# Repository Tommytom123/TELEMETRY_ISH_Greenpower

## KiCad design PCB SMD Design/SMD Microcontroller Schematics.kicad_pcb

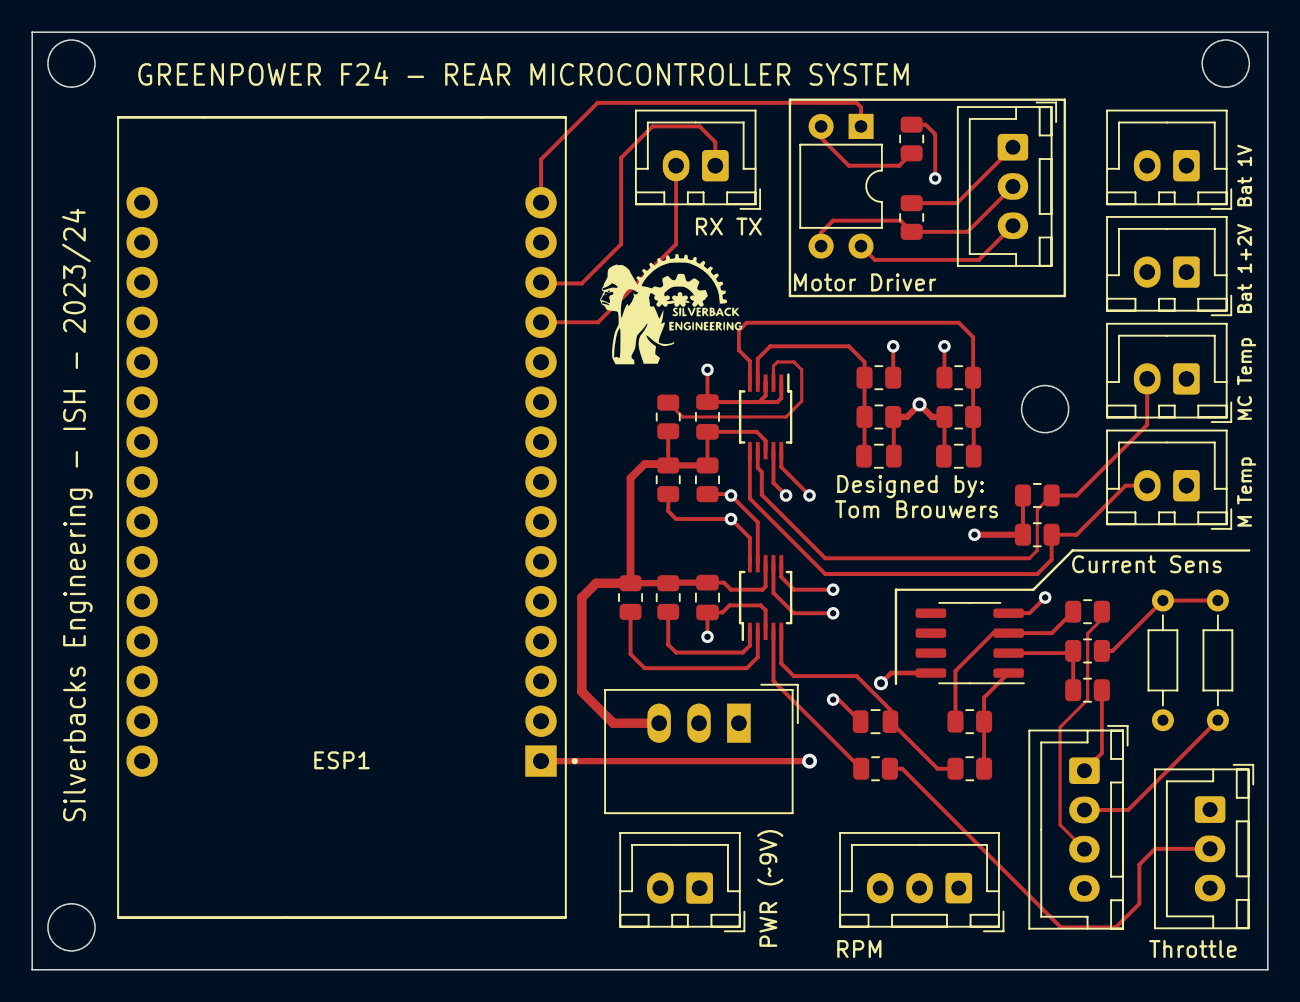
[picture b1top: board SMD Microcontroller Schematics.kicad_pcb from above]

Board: 4 copper layers, 78.7 x 59.7 mm, 42 parts (0 on the bottom side), 32 nets.

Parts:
C1, C2: C; C_0805_2012Metric
C3: 1u; C_0805_2012Metric
C4, C5: 100nF; C_0805_2012Metric
ESP1: ESP32-DEVKIT-V1; MODULE_ESP32_DEVKIT_V1
J1: Power (9v); JST_XH_B2B-XH-A_1x02_P2.50mm_Vertical
J2: Data (RX TX); JST_XH_B2B-XH-A_1x02_P2.50mm_Vertical
J3: RPM Sensor; JST_XH_B3B-XH-A_1x03_P2.50mm_Vertical
J4: Bat 1V; JST_XH_B2B-XH-A_1x02_P2.50mm_Vertical
J5: Bat 1+2 V; JST_XH_B2B-XH-A_1x02_P2.50mm_Vertical
J6: Motor Temp; JST_XH_B2B-XH-A_1x02_P2.50mm_Vertical
J7: Motor Controller Temp; JST_XH_B2B-XH-A_1x02_P2.50mm_Vertical
J8: Current Sensor; JST_XH_B4B-XH-A_1x04_P2.50mm_Vertical
J9: Motor Controller; JST_XH_B3B-XH-A_1x03_P2.50mm_Vertical
J10: Throttle HallEffect; JST_XH_B3B-XH-A_1x03_P2.50mm_Vertical
R1, R2, R3, R4, R5, R6: R; R_0805_2012Metric
R7, R8: 4.7k; R_0805_2012Metric
R9, R10, R15, R16, R17, R18, R19: 10k; R_0805_2012Metric
R11: 47k; R_0805_2012Metric
R12, R14: 1k; R_0805_2012Metric
R13: 220; R_0805_2012Metric
R20, R21: ?; R_Axial_DIN0204_L3.6mm_D1.6mm_P7.62mm_Horizontal
U1: TSR_1-2450; Converter_DCDC_TRACO_TSR-1_THT
U2: MCP6002DRG; SOIC-8_3.9x4.9mm_P1.27mm
U3: PC817; DIP-4_W7.62mm
U4, U5: ADS1115IDGS; TSSOP-10_3x3mm_P0.5mm

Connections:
3.3V: ESP1.1 (3V3), J3.3, R5.1, R6.1
5V: C4.1, C5.1, J8.4, J10.3, R15.1, R16.1, R17.1, R18.1, R19.1, U1.3 (Vout), U2.8 (V+), U4.8 (VDD), U5.8 (VDD)
9V: ESP1.30 (VIN), J1.2, U1.1 (Vin)
/Data: J9.2, R12.1, U3.3
/Motor5V: J9.3, U3.4
/MotorGND: J9.1, R12.2
Current: C3.1, R11.1, U5.5 (AIN1)
GND: C1.2, C2.2, C3.2, C4.2, C5.2, ESP1.2 (GND), ESP1.29 (GND), J1.1, J3.1, J4.1, J5.1, J6.1, J7.1, J8.1, J10.1, R2.2, R4.2, R9.2, R13.1, R21.1, U1.2 (GND), U2.4 (V-), U4.1 (ADDR), U4.3 (GND), U5.3 (GND)
GP19: ESP1.10 (D19), J3.2
GPIO 27 - PWM: ESP1.15 (D23), U3.1
Motor Controller Temp: J7.2, R6.2, U4.7 (AIN3)
Motor Temp: J6.2, R5.2, U4.6 (AIN2)
unnamed: ESP1.12 (RX0), J2.2
unnamed: ESP1.13 (TX0), J2.1
unnamed: J4.2, R1.1
unnamed: J5.2, R3.1
unnamed: J8.2, R20.1
unnamed: J8.3, R7.2
unnamed: J10.2, R14.1
unnamed: R10.1, R11.2, U2.1
unnamed: R13.2, U3.2
unnamed: R8.2, R20.2, R21.2
unnamed: R7.1, R10.2, U2.3 (+)
unnamed: R8.1, R9.1, U2.2 (-)
unnamed: R16.2, U4.2 (ALERT/RDY)
unnamed: R17.2, U5.1 (ADDR)
unnamed: R14.2, U5.4 (AIN0)
unnamed: R15.2, U5.2 (ALERT/RDY)
Reduced Bat1V: C1.1, R1.2, R2.1, U4.4 (AIN0)
Reduced TotalV: C2.1, R3.2, R4.1, U4.5 (AIN1)
SCL: ESP1.14 (D22), R18.2, U4.10 (SCL), U5.10 (SCL)
SDA: ESP1.11 (D21), R19.2, U4.9 (SDA), U5.9 (SDA)

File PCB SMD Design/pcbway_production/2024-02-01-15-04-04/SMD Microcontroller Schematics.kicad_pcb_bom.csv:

designator,quantity,value,pack,mpn,mount_type
"C1, C2",2,C,C_0805_2012Metric,,smt
C3,1,1u,C_0805_2012Metric,,smt
"C4, C5",2,100nF,C_0805_2012Metric,,smt
ESP1,1,ESP32-DEVKIT-V1,MODULE_ESP32_DEVKIT_V1,,tht
J1,1,Power (9v),JST_XH_B2B-XH-A_1x02_P2.50mm_Vertical,,tht
J10,1,Throttle HallEffect,JST_XH_B3B-XH-A_1x03_P2.50mm_Vertical,,tht
J2,1,Data (RX TX),JST_XH_B2B-XH-A_1x02_P2.50mm_Vertical,,tht
J3,1,RPM Sensor,JST_XH_B3B-XH-A_1x03_P2.50mm_Vertical,,tht
J4,1,Bat 1V,JST_XH_B2B-XH-A_1x02_P2.50mm_Vertical,,tht
J5,1,Bat 1+2 V,JST_XH_B2B-XH-A_1x02_P2.50mm_Vertical,,tht
J6,1,Motor Temp,JST_XH_B2B-XH-A_1x02_P2.50mm_Vertical,,tht
J7,1,Motor Controller Temp,JST_XH_B2B-XH-A_1x02_P2.50mm_Vertical,,tht
J8,1,Current Sensor,JST_XH_B4B-XH-A_1x04_P2.50mm_Vertical,,tht
J9,1,Motor Controller,JST_XH_B3B-XH-A_1x03_P2.50mm_Vertical,,tht
"R1, R2, R3, R4, R5, R6",6,R,R_0805_2012Metric,,smt
"R10, R15, R16, R17, R18, R19, R9",7,10k,R_0805_2012Metric,,smt
R11,1,47k,R_0805_2012Metric,,smt
"R12, R14",2,1k,R_0805_2012Metric,,smt
R13,1,220,R_0805_2012Metric,,smt
"R20, R21",2,?,R_Axial_DIN0204_L3.6mm_D1.6mm_P7.62mm_Horizontal,,tht
"R7, R8",2,4.7k,R_0805_2012Metric,,smt
U1,1,TSR_1-2450,Converter_DCDC_TRACO_TSR-1_THT,,tht
U2,1,MCP6002-xP,SOIC-8_3.9x4.9mm_P1.27mm,,smt
U3,1,PC817,DIP-4_W7.62mm,,tht
"U4, U5",2,ADS1115IDGS,TSSOP-10_3x3mm_P0.5mm,,smt

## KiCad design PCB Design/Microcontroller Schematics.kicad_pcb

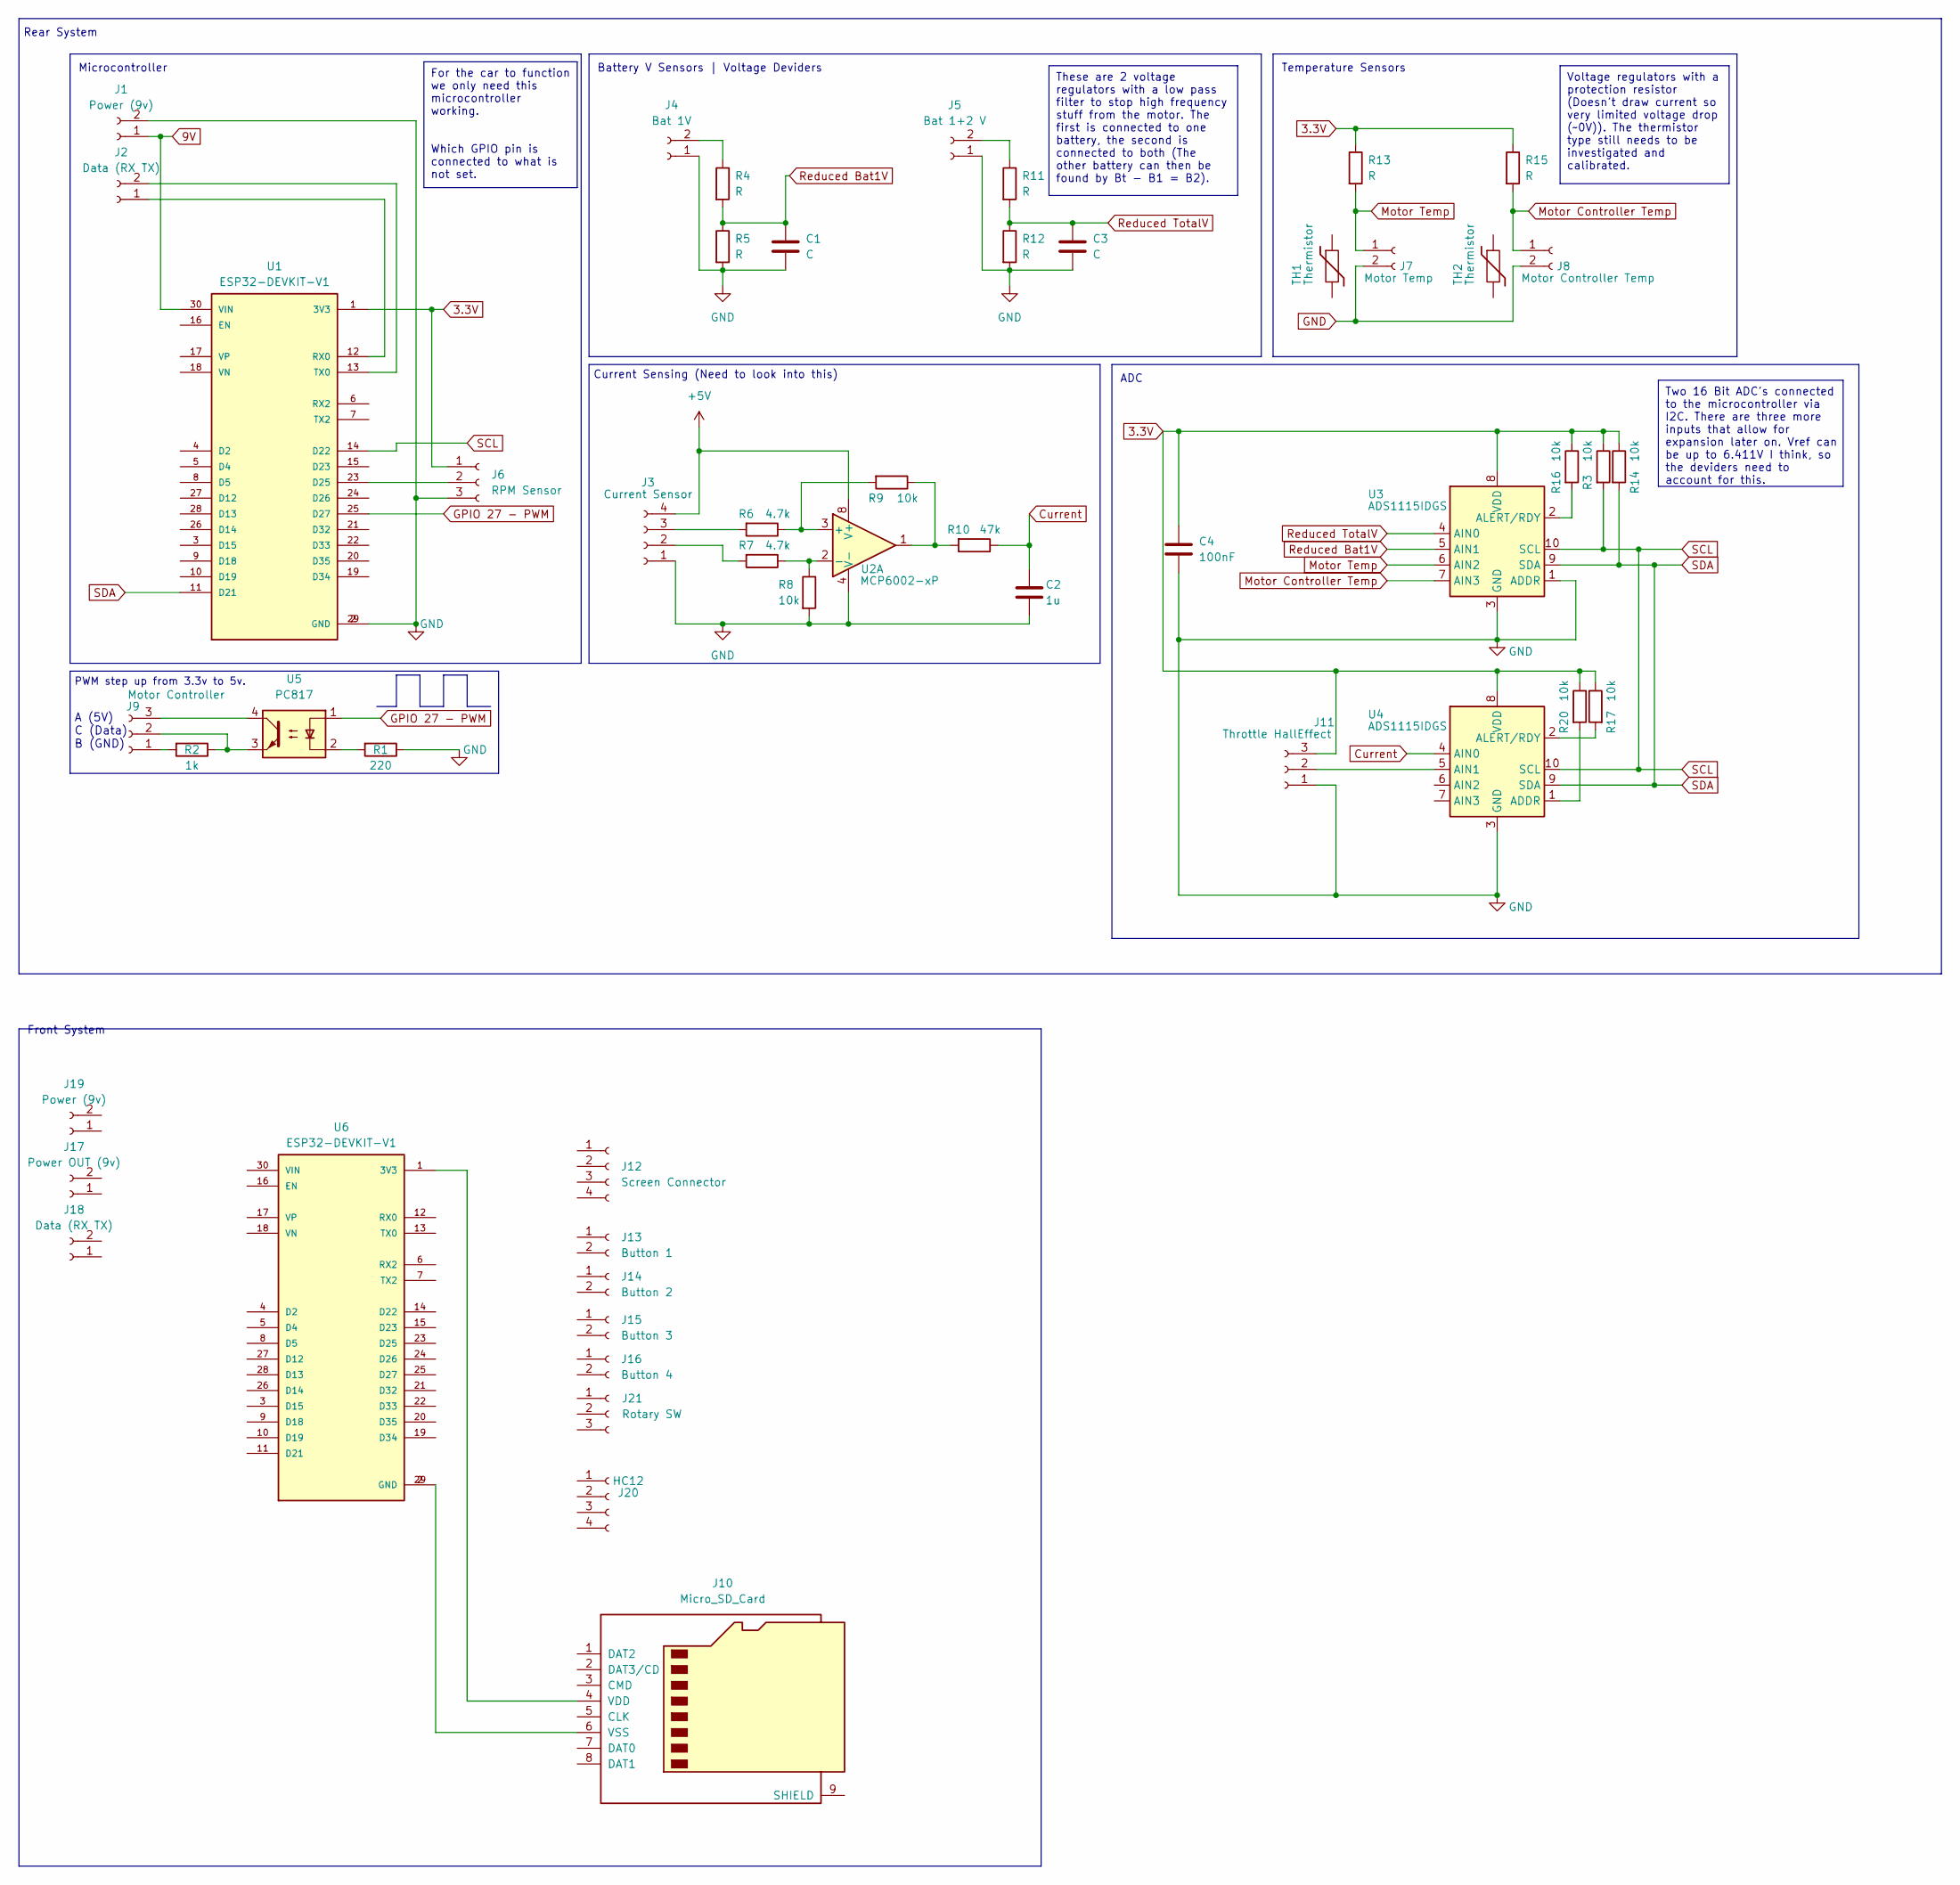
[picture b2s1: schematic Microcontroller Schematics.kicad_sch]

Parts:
C1, C3: C; C_Disc_D5.1mm_W3.2mm_P5.00mm
C2: 1u; C_Disc_D5.1mm_W3.2mm_P5.00mm
C4: 100nF; C_Disc_D5.1mm_W3.2mm_P5.00mm
J1, J19: Power (9v); JST_EH_S2B-EH_1x02_P2.50mm_Horizontal
J2, J18: Data (RX TX); JST_EH_S2B-EH_1x02_P2.50mm_Horizontal
J3: Current Sensor; JST_EH_S4B-EH_1x04_P2.50mm_Horizontal
J4: Bat 1V; JST_EH_S2B-EH_1x02_P2.50mm_Horizontal
J5: Bat 1+2 V; JST_EH_S2B-EH_1x02_P2.50mm_Horizontal
J6: RPM Sensor; JST_EH_S3B-EH_1x03_P2.50mm_Horizontal
J7: Motor Temp; JST_EH_S2B-EH_1x02_P2.50mm_Horizontal
J8: Motor Controller Temp; JST_EH_S2B-EH_1x02_P2.50mm_Horizontal
J9: Motor Controller; JST_EH_S3B-EH_1x03_P2.50mm_Horizontal
J10: Micro_SD_Card; microSD_HC_Hirose_DM3AT-SF-PEJM5
J11: Throttle HallEffect; JST_EH_S3B-EH_1x03_P2.50mm_Horizontal
J12: Screen Connector; JST_EH_S4B-EH_1x04_P2.50mm_Horizontal
J13: Button 1; JST_EH_S2B-EH_1x02_P2.50mm_Horizontal
J14: Button 2; JST_EH_S2B-EH_1x02_P2.50mm_Horizontal
J15: Button 3; JST_EH_S2B-EH_1x02_P2.50mm_Horizontal
J16: Button 4; JST_EH_S2B-EH_1x02_P2.50mm_Horizontal
J17: Power OUT (9v); JST_EH_S2B-EH_1x02_P2.50mm_Horizontal
J20: HC12; JST_EH_S4B-EH_1x04_P2.50mm_Horizontal
J21: Rotary SW; JST_EH_S3B-EH_1x03_P2.50mm_Horizontal
R1: 220; R_Axial_DIN0207_L6.3mm_D2.5mm_P10.16mm_Horizontal
R2: 1k; R_Axial_DIN0207_L6.3mm_D2.5mm_P10.16mm_Horizontal
R3, R8, R9, R14, R16, R17, R20: 10k; R_Axial_DIN0207_L6.3mm_D2.5mm_P10.16mm_Horizontal
R4, R5, R11, R12, R13, R15: R; R_Axial_DIN0207_L6.3mm_D2.5mm_P10.16mm_Horizontal
R6, R7: 4.7k; R_Axial_DIN0207_L6.3mm_D2.5mm_P10.16mm_Horizontal
R10: 47k; R_Axial_DIN0207_L6.3mm_D2.5mm_P10.16mm_Horizontal
TH1, TH2: Thermistor
U1, U6: ESP32-DEVKIT-V1; MODULE_ESP32_DEVKIT_V1; PARTREV N/A
U2: MCP6002-xP; DIP-8_W7.62mm_LongPads
U3, U4: ADS1115IDGS; TSSOP-10_3x3mm_P0.5mm
U5: PC817; DIP-4_W7.62mm

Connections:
3.3V: C4.1, J6.1, J11.3, R3.1, R13.1, R14.1, R15.1, R16.1, R17.1, R20.1, U1.1 (3V3), U3.8 (VDD), U4.8 (VDD)
9V: J1.1, U1.30 (VIN)
+5V: J3.4, U2.8 (V+)
Current: C2.1, R10.1, U4.4 (AIN0)
GND: C1.2, C2.2, C3.2, C4.2, J1.2, J3.1, J4.1, J5.1, J6.3, J7.2, J8.2, J11.1, R1.1, R5.2, R8.2, R12.2, U1.2 (GND), U1.29 (GND), U2.4 (V-), U3.1 (ADDR), U3.3 (GND), U4.3 (GND)
GPIO 27 - PWM: U1.25 (D27), U5.1
Motor Controller Temp: J8.1, R15.2, U3.7 (AIN3)
Motor Temp: J7.1, R13.2, U3.6 (AIN2)
unnamed: J2.1, U1.12 (RX0)
unnamed: J2.2, U1.13 (TX0)
unnamed: J3.2, R7.2
unnamed: J3.3, R6.2
unnamed: J4.2, R4.1
unnamed: J5.2, R11.1
unnamed: J6.2, U1.23 (D25)
unnamed: J9.1, R2.2
unnamed: J9.2, R2.1, U5.3
unnamed: J9.3, U5.4
unnamed: J10.4 (VDD), U6.1 (3V3)
unnamed: J10.6 (VSS), U6.2 (GND), U6.29 (GND)
unnamed: J11.2, U4.5 (AIN1)
unnamed: R1.2, U5.2
unnamed: R9.1, R10.2, U2.1
unnamed: R6.1, R9.2, U2.3 (+)
unnamed: R7.1, R8.1, U2.2 (-)
unnamed: R16.2, U3.2 (ALERT/RDY)
unnamed: R20.2, U4.1 (ADDR)
unnamed: R17.2, U4.2 (ALERT/RDY)
Reduced Bat1V: C1.1, R4.2, R5.1, U3.5 (AIN1)
Reduced TotalV: C3.1, R11.2, R12.1, U3.4 (AIN0)
SCL: R3.2, U1.14 (D22), U3.10 (SCL), U4.10 (SCL)
SDA: R14.2, U1.11 (D21), U3.9 (SDA), U4.9 (SDA)

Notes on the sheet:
For the car to function we only need this microcontroller working. Which GPIO pin is connected to what is not set.
Two 16 Bit ADC's connected to the microcontroller via I2C. There are three more inputs that allow for expansion later on. Vref can be up to 6.411V I think, so the deviders need to account for this.
These are 2 voltage regulators with a low pass filter to stop high frequency stuff from the motor. The first is connected to one battery, the second is connected to both (The other battery can then be found by Bt - B1 = B2).
Voltage regulators with a protection resistor (Doesn't draw current so very limited voltage drop (~0V)). The thermistor type still needs to be investigated and calibrated.
Rear System
ADC
Front System
A (5V) C (Data) B (GND)
PWM step up from 3.3v to 5v.
Temperature Sensors
Battery V Sensors | Voltage Deviders
Current Sensing (Need to look into this)
Microcontroller

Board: 2 copper layers, 49 parts (0 on the bottom side), 32 nets, no tracks yet.

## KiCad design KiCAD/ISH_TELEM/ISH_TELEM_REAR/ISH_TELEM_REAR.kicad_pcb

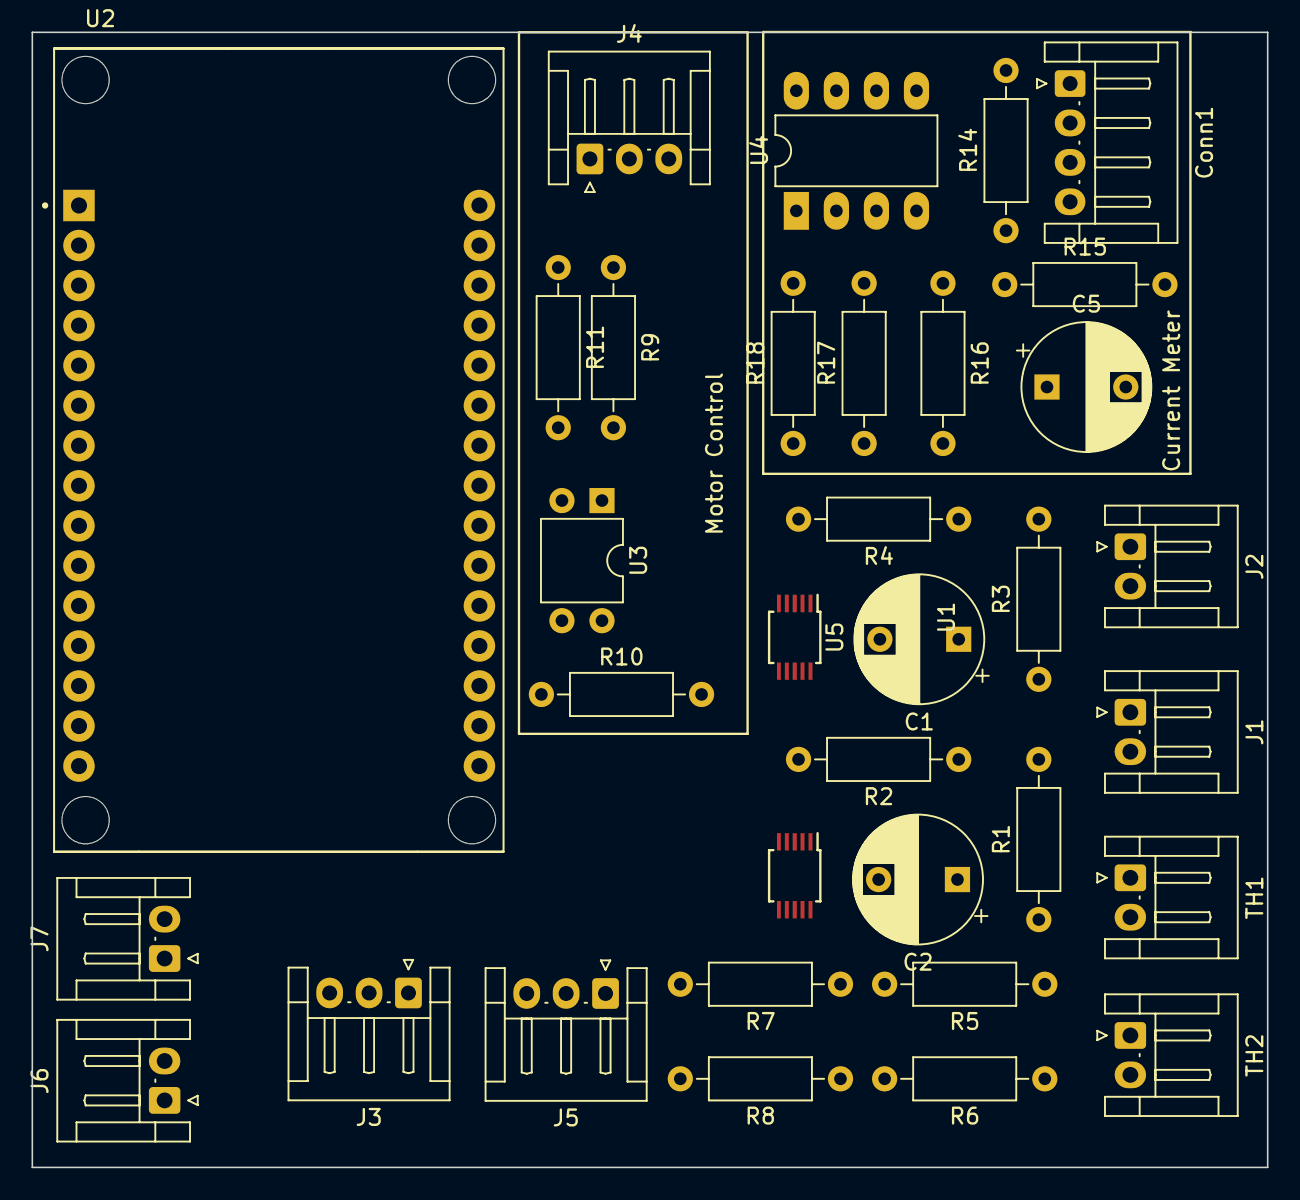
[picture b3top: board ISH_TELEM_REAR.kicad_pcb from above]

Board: 2 copper layers, 78.4 x 72.0 mm, 34 parts (0 on the bottom side), 24 nets, no tracks yet.

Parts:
C1, C2: C; CP_Radial_D8.0mm_P5.00mm
C5: 1u; CP_Radial_D8.0mm_P5.00mm
Conn1: Current; JST_EH_S4B-EH_1x04_P2.50mm_Horizontal
J1: Battery 1 (12V); JST_EH_S2B-EH_1x02_P2.50mm_Horizontal
J2: Battery 1+2 (24V); JST_EH_S2B-EH_1x02_P2.50mm_Horizontal
J3: RPM Connector; JST_EH_S3B-EH_1x03_P2.50mm_Horizontal
J4: Motor PINS; JST_EH_S3B-EH_1x03_P2.50mm_Horizontal
J5: Throttle Trigger; JST_EH_S3B-EH_1x03_P2.50mm_Horizontal
J6: DATA; JST_EH_S2B-EH_1x02_P2.50mm_Horizontal
J7: POWER; JST_EH_S2B-EH_1x02_P2.50mm_Horizontal
R1, R2, R3, R4, R5, R6, R7, R8: R; R_Axial_DIN0207_L6.3mm_D2.5mm_P10.16mm_Horizontal
R9: 10K; R_Axial_DIN0207_L6.3mm_D2.5mm_P10.16mm_Horizontal
R10: ~0.4K; R_Axial_DIN0207_L6.3mm_D2.5mm_P10.16mm_Horizontal
R11: ~10K; R_Axial_DIN0207_L6.3mm_D2.5mm_P10.16mm_Horizontal
R14, R15: 4.7k; R_Axial_DIN0207_L6.3mm_D2.5mm_P10.16mm_Horizontal
R16, R17: 10k; R_Axial_DIN0207_L6.3mm_D2.5mm_P10.16mm_Horizontal
R18: 47k; R_Axial_DIN0207_L6.3mm_D2.5mm_P10.16mm_Horizontal
TH1, TH2: Thermistor; JST_EH_S2B-EH_1x02_P2.50mm_Horizontal
U1, U5: ADS1115IDGS; TSSOP-10_3x3mm_P0.5mm
U2: ESP32-DEVKIT-V1; MODULE_ESP32_DEVKIT_V1
U3: PC817; DIP-4_W7.62mm
U4: MCP6002-xP; DIP-8_W7.62mm_LongPads

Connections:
3.3V: J3.1, J5.1, R5.1, R6.1, U2.1 (3V3)
+5V: Conn1.1, U4.8 (V+)
B (GND): J4.3, R9.2, R11.2
Battery1 (12V): J1.1, R1.1
Battery1+2 (24V): J2.1, R3.1
C (Data): J4.2, R11.1, U3.3
Current: C5.1, R18.1, U5.4 (AIN0)
D (5V): J4.1, R9.1, U3.4
GND: C1.2, C2.2, C5.2, Conn1.4, J1.2, J2.2, J3.2, J5.3, J7.2, R2.2, R4.2, R16.2, TH1.2, TH2.2, U1.1 (ADDR), U1.3 (GND), U2.2 (GND), U2.29 (GND), U3.2, U4.4 (V-), U5.3 (GND)
GPIO 27 - PWM: R10.1, U2.25 (D27)
Motor Controller Temp: R8.2, U1.7 (AIN3)
Motor Temp: R7.2, U1.6 (AIN2)
unnamed: Conn1.2, R14.2
unnamed: Conn1.3, R15.2
unnamed: R5.2, R7.1, TH1.1
unnamed: R6.2, R8.1, TH2.1
unnamed: R10.2, U3.1
unnamed: R17.1, R18.2, U4.1
unnamed: R14.1, R17.2, U4.3 (+)
unnamed: R15.1, R16.1, U4.2 (-)
Reduced Bat1V: C1.1, R1.2, R2.1, U1.5 (AIN1)
Reduced TotalV: C2.1, R3.2, R4.1, U1.4 (AIN0)
Throttle Pot / Hall effect: J5.2, U5.7 (AIN3)
Vin (9V): J7.1, U1.8 (VDD), U2.30 (VIN), U5.1 (ADDR), U5.8 (VDD)

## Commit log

2023-10-08 Adding Motor Stuff
2023-10-10 Added throttle percentage
2023-10-10 Fixed the bouncing of RPM and speed
2023-10-16 Adding Multicontroller approach
2023-10-16 Calibration
    Also accel has issues, so not sure if that should be recorded
2023-10-16 Cleaner and added pages for the buttons
2023-10-27 Added KiCAD SCHEMATICS!!!
2023-10-28 Added schematic for the front pcb thing
2023-10-28 Some changes
2023-10-29 Changed some stuff for the ADC
2023-10-30 Started understanding the current sens stuff, and made a few adjustments
2023-11-01 Small changes
2023-11-02 Make sure you don't push when a schematic is open
2023-11-09 Changed some V step up stuff
2023-11-29 Moved to ESP32
2023-12-01 Trying to get the SD card to work again...
2023-12-01 SD CARD WORKS
    SD.open (FILE_WRITE) is different for an arduino and ESP...
2023-12-02 MAJOR CHANGES - Improved collaborative Framework
2023-12-02 Improved file creation
    Added ability to number the telem file, so overwriting doesn't happen
2023-12-04 Did some organization and renaming
2023-12-06 Test
2023-12-06 Simple Working RX and TX
2023-12-06 Uploaded Display Sketch
2023-12-07 Moved The individual files in their respective folders
2023-12-07 Incorporated Transmission and Display elements
    The code compiles, but I have not checked if it runs.
2023-12-07 Didn't change much
2023-12-09 Added some comments and some temporary changes
2023-12-09 Updated the KICAD schematic
    Added the working PWM amplifier and replaced the Microcontroller with ESP32
2023-12-12 Changed Button
2023-12-16 Worked on the PCB Design
2023-12-16 Added latest changes from other branch
2023-12-17 Remaking the PCB schematic for better clarity
2023-12-17 Working on remaking the schematics
2023-12-18 Remade the through hole (TH) PCB
2023-12-20 PCB changes
2024-05-22 Many Changes
2024-05-31 Added FEC, Escaping and Transmit Functions
